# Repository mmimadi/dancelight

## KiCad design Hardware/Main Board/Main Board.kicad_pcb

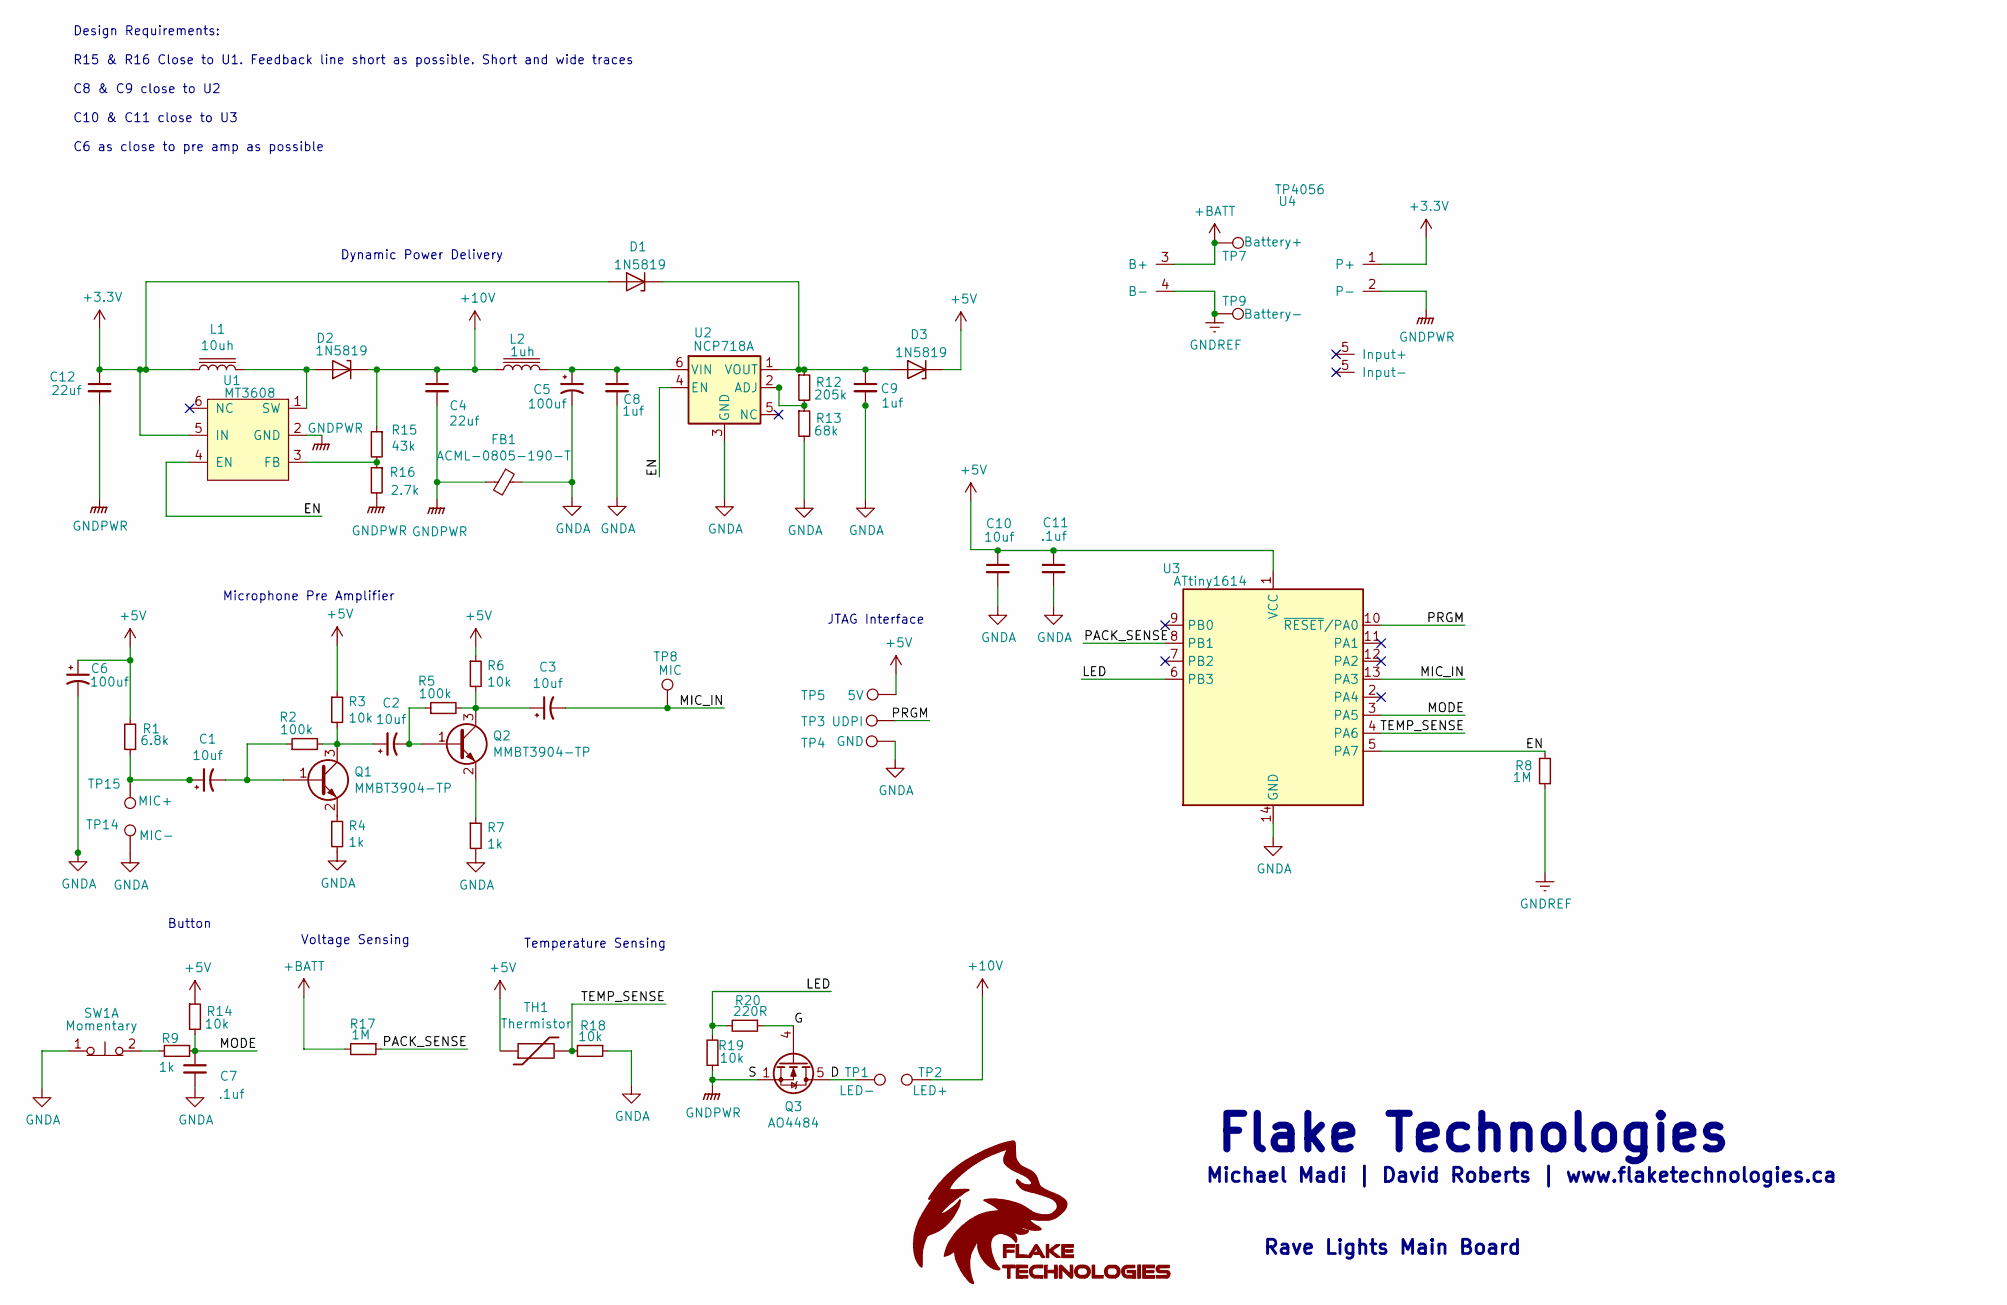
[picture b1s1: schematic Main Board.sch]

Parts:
C1, C2, C3: 10uf; CP_Elec_4x5.3
C4, C12: 22uf; C_0805_2012Metric
C5, C6: 100uf; CP_Elec_6.3x7.7
C7, C11: .1uf; C_0603_1608Metric
C8, C9: 1uf; C_0603_1608Metric
C10: 10uf; C_0603_1608Metric
D1, D2, D3: 1N5819; D_SOD-323
FB1: ACML-0805-190-T; R_0603_1608Metric
L1: 10uh; L_Sunlord_MWSA0518_5.4x5.2mm
L2: 1uh; L_0805_2012Metric
Q1, Q2: MMBT3904-TP; SOT-23
Q3: AO4484; SOIC-8_3.9x4.9mm_P1.27mm
R1: 6.8k; R_0603_1608Metric
R2, R5: 100k; R_0603_1608Metric
R3, R6, R14, R18, R19: 10k; R_0603_1608Metric
R4, R7, R9: 1k; R_0603_1608Metric
R8, R17: 1M; R_0603_1608Metric
R12: 205k; R_0603_1608Metric
R13: 68k; R_0603_1608Metric
R15: 43k; R_0603_1608Metric
R16: 2.7k; R_0603_1608Metric
R20: 220R; R_0603_1608Metric
SW1: Momentary; tactile
TH1: Thermistor; C_0805_2012Metric
TP1: LED-; TestPoint_Pad_3.0x3.0mm
TP2: LED+; TestPoint_Pad_3.0x3.0mm
TP3: UDPI; TestPoint_Pad_D2.5mm
TP4: GND; TestPoint_Pad_D2.5mm
TP5: 5V; TestPoint_Pad_D2.5mm
TP7: Battery+; TestPoint_Pad_3.0x3.0mm
TP8: MIC; TestPoint_Pad_D2.0mm
TP9: Battery-; TestPoint_Pad_3.0x3.0mm
TP14: MIC+; TestPoint_Keystone_5019_Minature
TP15: MIC-; TestPoint_Keystone_5019_Minature
U1: MT3608; SOT-23-6
U2: NCP718A; SON65P200X200X80-7N
U3: ATtiny1614; SOIC-14_3.9x8.7mm_P1.27mm
U4: TP4056; charger

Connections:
+3V3: C12.1, D1.2 (A), L1.2, U1.5 (IN), U4.1 (P+)
+5V: C6.1, C10.1, C11.1, D3.1 (K), R1.2, R3.1, R6.1, R14.1, TH1.1, TP5.1, U3.1 (VCC)
+10V: C4.1, D2.1 (K), L2.2, R15.1, TP2.1
+BATT: R17.2, TP7.1, U4.3 (B+)
/D: Q3.5 (D), TP1.1
/EN: R8.2, U1.4 (EN), U2.4 (EN), U3.5 (PA7)
/G: Q3.4 (G), R20.1
/LED: R19.2, R20.2, U3.6 (PB3)
/MIC_IN: C3.2, TP8.1, U3.13 (PA3)
/MODE: C7.1, R9.1, R14.2, U3.3 (PA5)
/PACK_SENSE: R17.1, U3.8 (PB1)
/PRGM: TP3.1, U3.10 (~RESET~/PA0)
/TEMP_SENSE: R18.2, TH1.2, U3.4 (PA6)
GNDA: C5.2, C6.2, C7.2, C8.2, C9.2, C10.2, C11.2, FB1.1, R4.2, R7.2, R13.2, R18.1, SW1.1, TP4.1, TP15.1, U2.3 (GND), U3.14 (GND)
GNDPWR: C4.2, C12.2, FB1.2, Q3.1 (S), Q3.2 (S), Q3.3 (S), R16.2, R19.1, U1.2 (GND), U4.2 (P-)
GNDREF: R8.1, TP9.1, U4.4 (B-)
unnamed: C1.1, R1.1, TP14.1
unnamed: C1.2, Q1.1 (B), R2.1
unnamed: C2.1, Q1.3 (C), R2.2, R3.2
unnamed: C2.2, Q2.1 (B), R5.1
unnamed: C3.1, Q2.3 (C), R5.2, R6.2
unnamed: C5.1, C8.1, L2.1, U2.6 (VIN)
unnamed: C9.1, D1.1 (K), D3.2 (A), R12.1, U2.1 (VOUT)
unnamed: D2.2 (A), L1.1, U1.1 (SW)
unnamed: Q1.2 (E), R4.1
unnamed: Q2.2 (E), R7.1
unnamed: R9.2, SW1.2
unnamed: R12.2, R13.1, U2.2 (ADJ)
unnamed: R15.2, R16.1, U1.3 (FB)

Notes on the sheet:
Microphone Pre Amplifier
Voltage Sensing
Temperature Sensing
Button
Michael Madi | David Roberts | www.flaketechnologies.ca
Rave Lights Main Board
JTAG Interface
Dynamic Power Delivery
Design Requirements: R15 & R16 Close to U1. Feedback line short as possible. Short and wide traces C8 & C9 close to U2 C10 & C11 close to U3 C6 as close to pre amp as possible
Flake Technologies

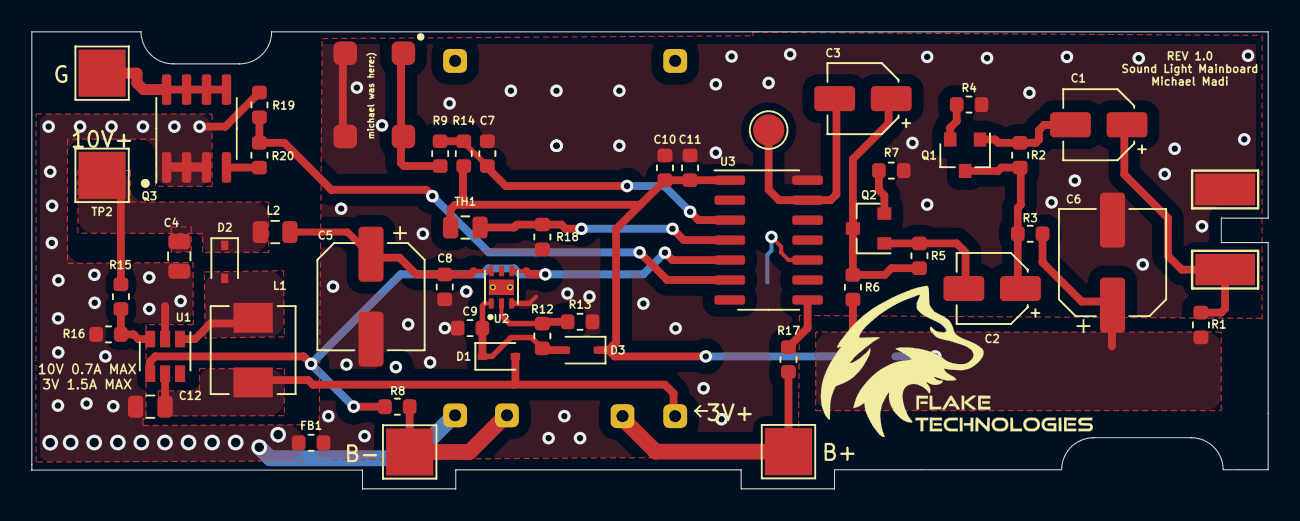
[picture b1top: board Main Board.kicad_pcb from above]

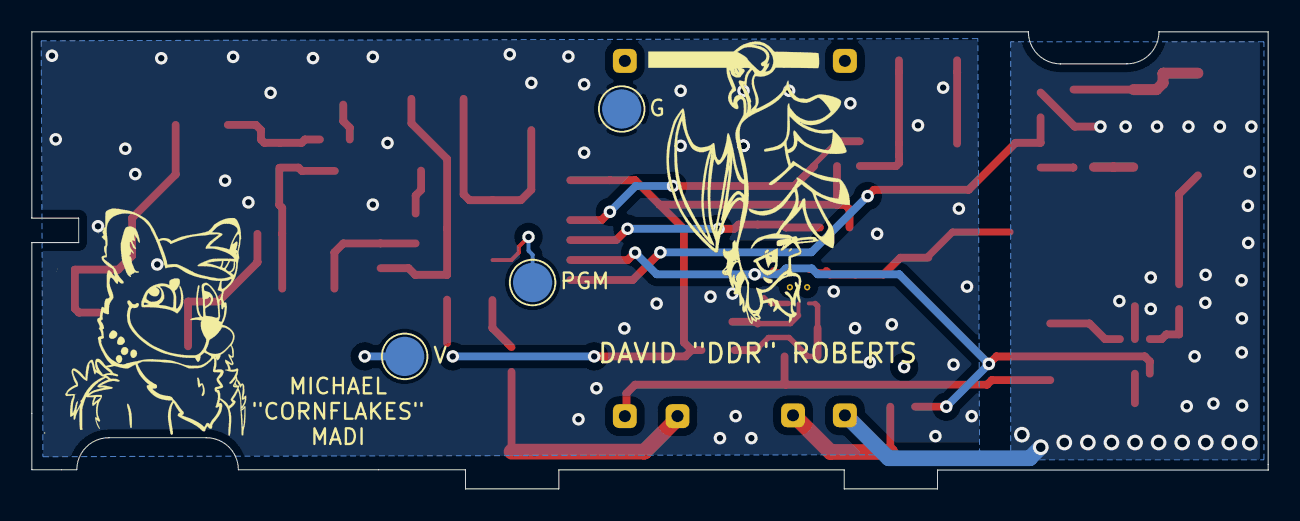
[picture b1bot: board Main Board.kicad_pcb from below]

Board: 2 copper layers, 78.7 x 29.1 mm, 55 parts (3 on the bottom side), 29 nets.

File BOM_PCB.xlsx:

BOM
Rave Light Driver PCB Main Board |  | Fix: 22uf to 0805 on board
Rev 1 |  | Find 1uf 2A inductor
Reference | Value/Part Number | Footprint | MPN | Datasheet | Source | Notes
C1, C2, C3 | 10uf | Capacitor_SMD:CP_Elec_4x5.3 | VE-100M1ETR-0405 | ~
C4, C12 | 22uf | Capacitor_SMD:C_0603_1608Metric | CL21A226MAQNNNE | ~
C5, C6 | 100uf | Capacitor_SMD:CP_Elec_6.3x7.7 | VES101M1ETR-0607 | ~
C8, C9 | 1uf | Capacitor_SMD:C_0603_1608Metric | CL10A105KB8NNNC | ~
C10 | 10uf | Capacitor_SMD:C_0603_1608Metric | CL10A106KP8NNNC | ~
C7, C11 | .1uf | Capacitor_SMD:C_0603_1608Metric | CC0603KRX7R9BB104 | ~
D1, D2, D3 | 1N5819 | Diode_SMD:D_SOD-323 | 1N5819WS | ~
FB1 | 2A Ferrite Bead | Resistor_SMD:R_0805_2012Metric | BLM18PG121SN1D | ~
L1 | 10uh | Inductor_SMD:L_Sunlord_MWSA0518_5.4x5.2mm | MWSA0503-100MT | ~
L2 | 1uh | Inductor_SMD:L_0805_2012Metric | figure out | ~
Q1, Q2 | MMBT3904-TP | Package_TO_SOT_SMD:SOT-23 | MMBT3904-TP | ~
Q3 | AO4484 | Main Board1:SOIC-8_3.9x4.9mm_P1.27mm | AO4484 | http://www.ti.com/lit/gpn/csd16342q5a
R1 | 6.8k | Resistor_SMD:R_0603_1608Metric | 0603WAF6801T5E | ~
R2, R5 | 100k | Resistor_SMD:R_0603_1608Metric | 0603WAF1003T5E | ~
R3, R6, R14, R18, R19 | 10k | Resistor_SMD:R_0603_1608Metric | 0603WAF1002T5E | ~
R4, R7, R9 | 1k | Resistor_SMD:R_0603_1608Metric | 0603WAF1001T5E | ~
R12 | 205k | Resistor_SMD:R_0603_1608Metric | 0603WAF2053T5E | ~
R13 | 68k | Resistor_SMD:R_0603_1608Metric | 0603WAF6802T5E | ~
R15 | 43k | Resistor_SMD:R_0603_1608Metric | 0603WAF4302T5E | ~
R16 | 2.7k | Resistor_SMD:R_0603_1608Metric | 0603WAF2701T5E | ~
R8, R17 | 1M | Resistor_SMD:R_0603_1608Metric | 0603WAF1004T5E | ~
R20 | 220R | Resistor_SMD:R_0603_1608Metric | 0603WAF2200T5E | ~
SW1 | Momentary | Main Board1:tactile | TS-1187A-C-E-B | ~
TH1 | Thermistor | Capacitor_SMD:C_0805_2012Metric | NTCG163JF103FT1 | ~

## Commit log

2020-04-30 Initial commit.
2020-04-30 organization
2020-04-30 names
2020-05-01 added auto tune stil needs lots of work
2020-05-01 Combined Cornflakes' sound-detection code and DDR's pattern blink code.
2020-05-01 Merged changes into combined from 99767fd.
2020-05-01 updated expenses
2020-05-02 sexy revision for sound reaction
2020-05-02 fade for sound light
2020-05-02 merged code
2020-05-06 schematic
2020-05-08 schemaic
2020-05-08 sound code updates
2020-05-08 Tweaked sound_reaction to work as a loop. Untested.
    - I don't have a mic here.
2020-05-10 stuff
2020-05-12 shcmeatic tuning
2020-05-12 sound code average
2020-05-13 Added fade effect to sound_reaction.ino; broke beat detection. 😒😷
2020-05-13 push from surface
2020-05-13 stuff and things and fixes for sound_reaction_fade
2020-05-13 to do
2020-05-14 failed boost converter
2020-05-15 Made sound_reaction_fade have an instant mode, like sound_reaction.
2020-05-15 Added an untested version of floating beat detection.
    (For 100 samples, beat if sample - min > (max - min) * 0.9.)
2020-05-15 Fixed qsort comparison function.
2020-05-15 added boost converter, button and ton of work to schematic
2020-05-16 schematic done. just calculate values now
2020-05-20 calculated values for schematic
2020-05-20 Voltage read code, expenses and voltage divider for linear reg update
2020-05-25 fixed calculations and updated expense
2020-05-28 work on boost
2020-05-29 work on sorting for volume envelope detection
2020-05-29 Fixed sound_reaction_fade statistics function.
2020-05-29 pre amp rtest code update
2020-05-29 sound_reaction_fade w/ full debugging @ 57600 baud
    - upper/lower beat detection
    - instant fade
2020-06-01 added feature list
2020-06-02 feature list and hardware to do
2020-06-05 Updated DC-DC design, updated MCU and added datasheets
2020-06-09 datasheeets
2020-06-15 Huge changes to schematic!
2020-06-15 Added JTAG programming interface and decoupling cap on amp supply
2020-06-16 started core functions code
2020-06-17 Made ring buffer work better with cutofs and stuff. ❤
2020-06-17 Completed button handling code with inturupts
2020-06-17 Completed button handling code with inturupts and replaced pre_amp_test with Benchmark 😍😍😍
2020-06-18 EEPROM + New button added to combined ✌✌
2020-06-19 Renamed combined, removed extraneous file extension.
2020-06-19 combined.ino: Merged in sound_reaction_fade.ino.
    - Split combined.ino into files, corresponding
    to functionality. They're still all global,
    mind you, but details. It might be time to
    get classes involved here.
    - I don't have the button hardware here, so I
    haven't really tested that code works.
2020-06-19 Removed some old/test firmware.
2020-06-19 Fixed char -> string mistake.
2020-06-19 Removed processAudio (exponential beat detection.)
2020-06-19 Got memory usage below 8kb.
2020-06-19 removed exponential sound react
2020-06-19 minor adjustments
2020-06-20 Removed more preset patterns due to memory restrictions.
2020-06-20 minor changes
2020-06-23 started low power mode but wont turn on again after being turned off 😢😢
2020-06-23 improved boot and shut down animations, fixed eeprom bug, check battery by double tapping even if off, psu fault checking for production, added tap to wake and now defaults to ON while we work on stu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
2020-06-25 fixed modes and improved animations and other tiny improvments
2020-06-26 voltage checking is now active with a double press! Can now boot device even if wake up light is active
2020-06-26 Switched to C++ from Arduino Sketch, for the most part.
    - This means, mostly, that we have I think per-file namespaces now?
2020-06-27 Removed old time-based button code as new cycle-based code works fine. :)
2020-06-27 Converted our modes to classes.
    - Now they don't all have to be in memory at once! \o/
    - Also, this is the first time I've really designed my own C++
    class hierarchy, so it's a bit rough.
2020-06-27 Moved power sequence stuff into own class.
    - Pulled all pins into common.hpp, so they're together.
2020-06-27 added footprints to schematic. Some still need to be made but mostly all are done
2020-06-28 added a few more footprints before I got drunk and forgot to push lol
2020-07-01 Added mic2serial pipe program.
2020-07-01 Tried to add Goertzel detection routine, but getting nonsensical error.
    - goertzel_detection_mode.cpp:11:28: error: no matching function
    for call to 'Goertzel::Goertzel()'
    - This doesn't make any sense, because this is never called
    in this manner. It's always got three floats in it.
2020-07-01 Fixed compile. (re error: no matching function for call)
2020-07-01 Added goertzel-based frequency detection mode. It doesn't work to detect beat.
2020-07-01 Added base code for take 3 of beat detection. We got thisgit add .!
2020-07-02 Imported Cornflakes' Beat Detection v3 into combined.ino.
2020-07-02 Fixed up bandpass filter mode from beat detection v3 so that it doesn't monopolize the main loop.
2020-07-03 Made bandpass mode fade like goertzel beat detection mode.
2020-07-03 placed PCB
2020-07-07 coper fills on PCB
2020-07-07 almost done pcb
2020-07-10 PCB completed and ready for reviewgit add .git add .
2020-07-15 fixed benchmark
2020-07-17 PCB fixeruppers
2020-07-26 added marketing folder. we should maybe make a G drive soon if we start filling up.
2020-07-29 board review done, almost done BOM and component map.
2020-07-29 Broke out max duty cycle variable and exposed volume to bandpass filter beat mode.
2020-07-30 board sent for production
2020-08-01 Made blink mode work in like 1/3rd of the space.
2020-08-01 Removed plotting output from blink mode.
2020-08-01 Removed some stray cache files.
2020-08-04 expenses update
2020-08-12 added compatibility for the main board. button a little fucked tho
2020-08-19 commented where the ADC settings need to be updated
2020-08-26 Slowed blink down to something little less crazed.
2020-08-26 Made blink respect maxDutyCycle.
2020-08-26 Made solid mode max brightness - 55 to save on power.
2020-08-26 Added the ref sheet for microprocesser we're actually using.
2020-08-26 Removed failed ring buffer and goertzel detection modes.
2020-08-26 Corrected issue wrt blink pattern only using presets #4 and #5.
2020-08-26 tried to fix the registers
2020-08-26 Added a #DEFINE in common.hpp so we can switch between dev and prod boards.
2020-08-26 Partially revert c87fec4d88ab7429b1dd00c26c663de7dc687d3d.
    - For some reason, all bytes in power_sequences.cpp were null.
2020-08-26 Added Arduino Nano chip datasheet.
2020-08-27 interem fixed to bandpass filter beat
2020-08-30 Improvements to beat detection; elimination of double-bounce issue.
2020-08-30 Added rough estimate for bias for prod boards.
2020-08-30 Removed unused preset pattern state machine.
2020-08-30 whatever changes we made last night when we hung out. I think some confidence levels
2020-08-30 Auto bias. (It semes to wander a bit.)
2020-08-31 Further tuning to the beat detection mode.
2020-08-31 Reverted power_sequences back to an .ino, so no cpp/hpp object bs.
2020-08-31 Added beat frequency fading + fallback when no beat.
